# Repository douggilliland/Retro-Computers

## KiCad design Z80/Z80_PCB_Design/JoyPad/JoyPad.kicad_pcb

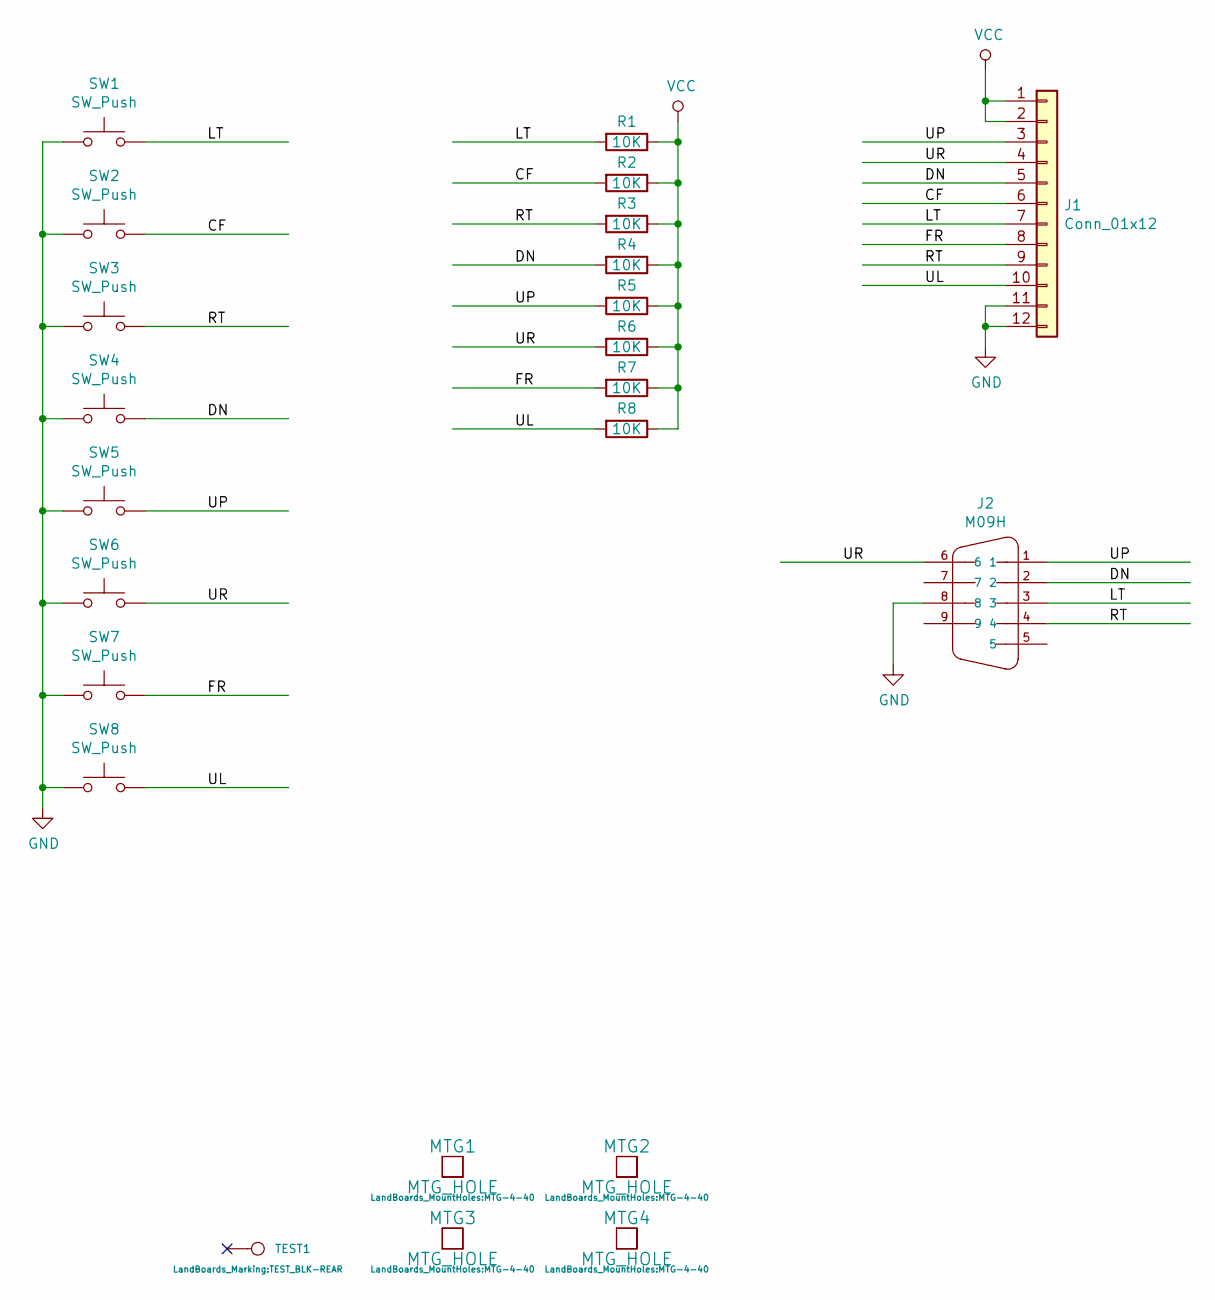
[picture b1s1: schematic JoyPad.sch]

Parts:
J1: Conn_01x12; PinHeader_1x12_P2.54mm_Vertical
J2: M09H; DSUB-9_Male_Horizontal_P2.77x2.84mm_EdgePinOffset4.94mm_Hou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
MTG1, MTG2, MTG3, MTG4: MTG_HOLE; MTG-4-40
R1, R2, R3, R4, R5, R6, R7, R8: 10K; R_0805_2012Metric_Pad1.15x1.40mm_HandSolder
SW1, SW2, SW3, SW4, SW5, SW6, SW7, SW8: SW_Push; SW_PUSH_6mm
TEST1: CONN_1; TEST_BLK-REAR

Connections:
/CF: J1.6, R2.2, SW2.2
/DN: J1.5, J2.2, R4.2, SW4.2
/FR: J1.8, R7.2, SW7.2
/LT: J1.7, J2.3, R1.2, SW1.2
/RT: J1.9, J2.4, R3.2, SW3.2
/UL: J1.10, R8.2, SW8.2
/UP: J1.3, J2.1, R5.2, SW5.2
/UR: J1.4, J2.6, R6.2, SW6.2
GND: J1.11, J1.12, J2.8, SW1.1, SW2.1, SW3.1, SW4.1, SW5.1, SW6.1, SW7.1, SW8.1
VCC: J1.1, J1.2, R1.1, R2.1, R3.1, R4.1, R5.1, R6.1, R7.1, R8.1

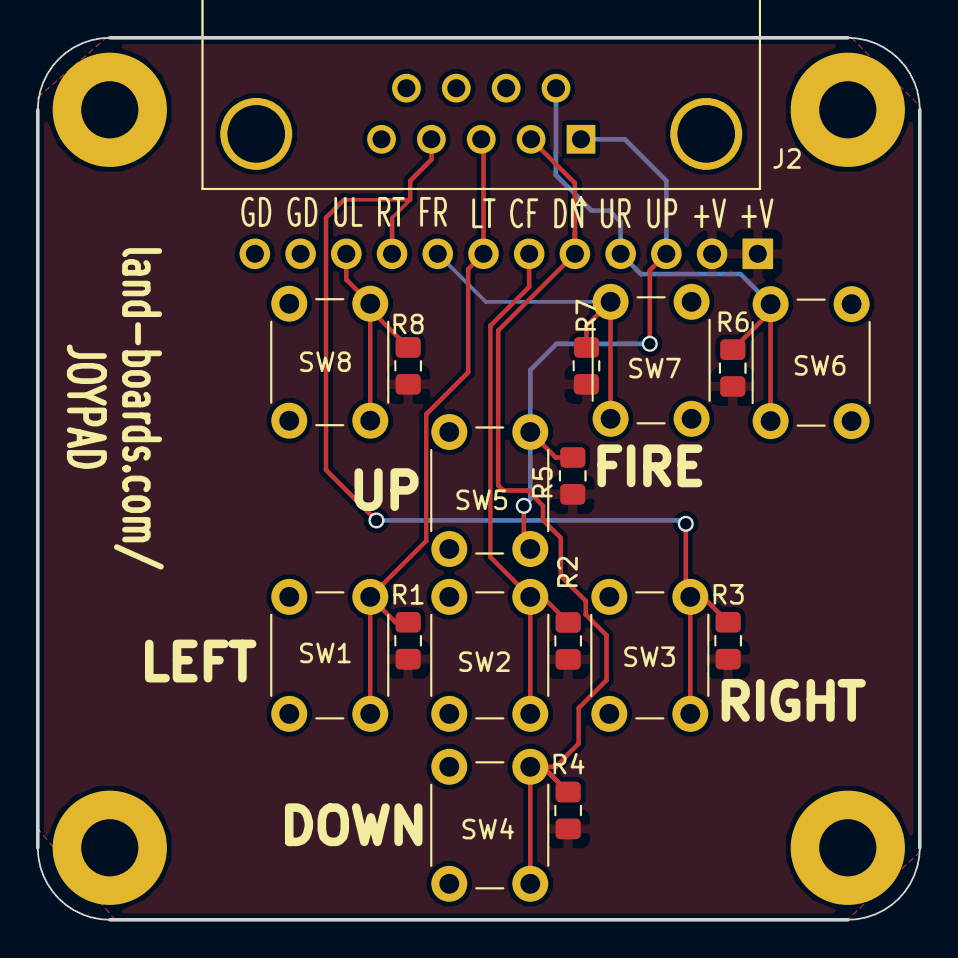
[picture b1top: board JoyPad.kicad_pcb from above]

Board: 2 copper layers, 49.0 x 49.0 mm, 23 parts (1 on the bottom side), 10 nets.

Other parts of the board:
TEST: CONN_1; TEST_BLK-REAR

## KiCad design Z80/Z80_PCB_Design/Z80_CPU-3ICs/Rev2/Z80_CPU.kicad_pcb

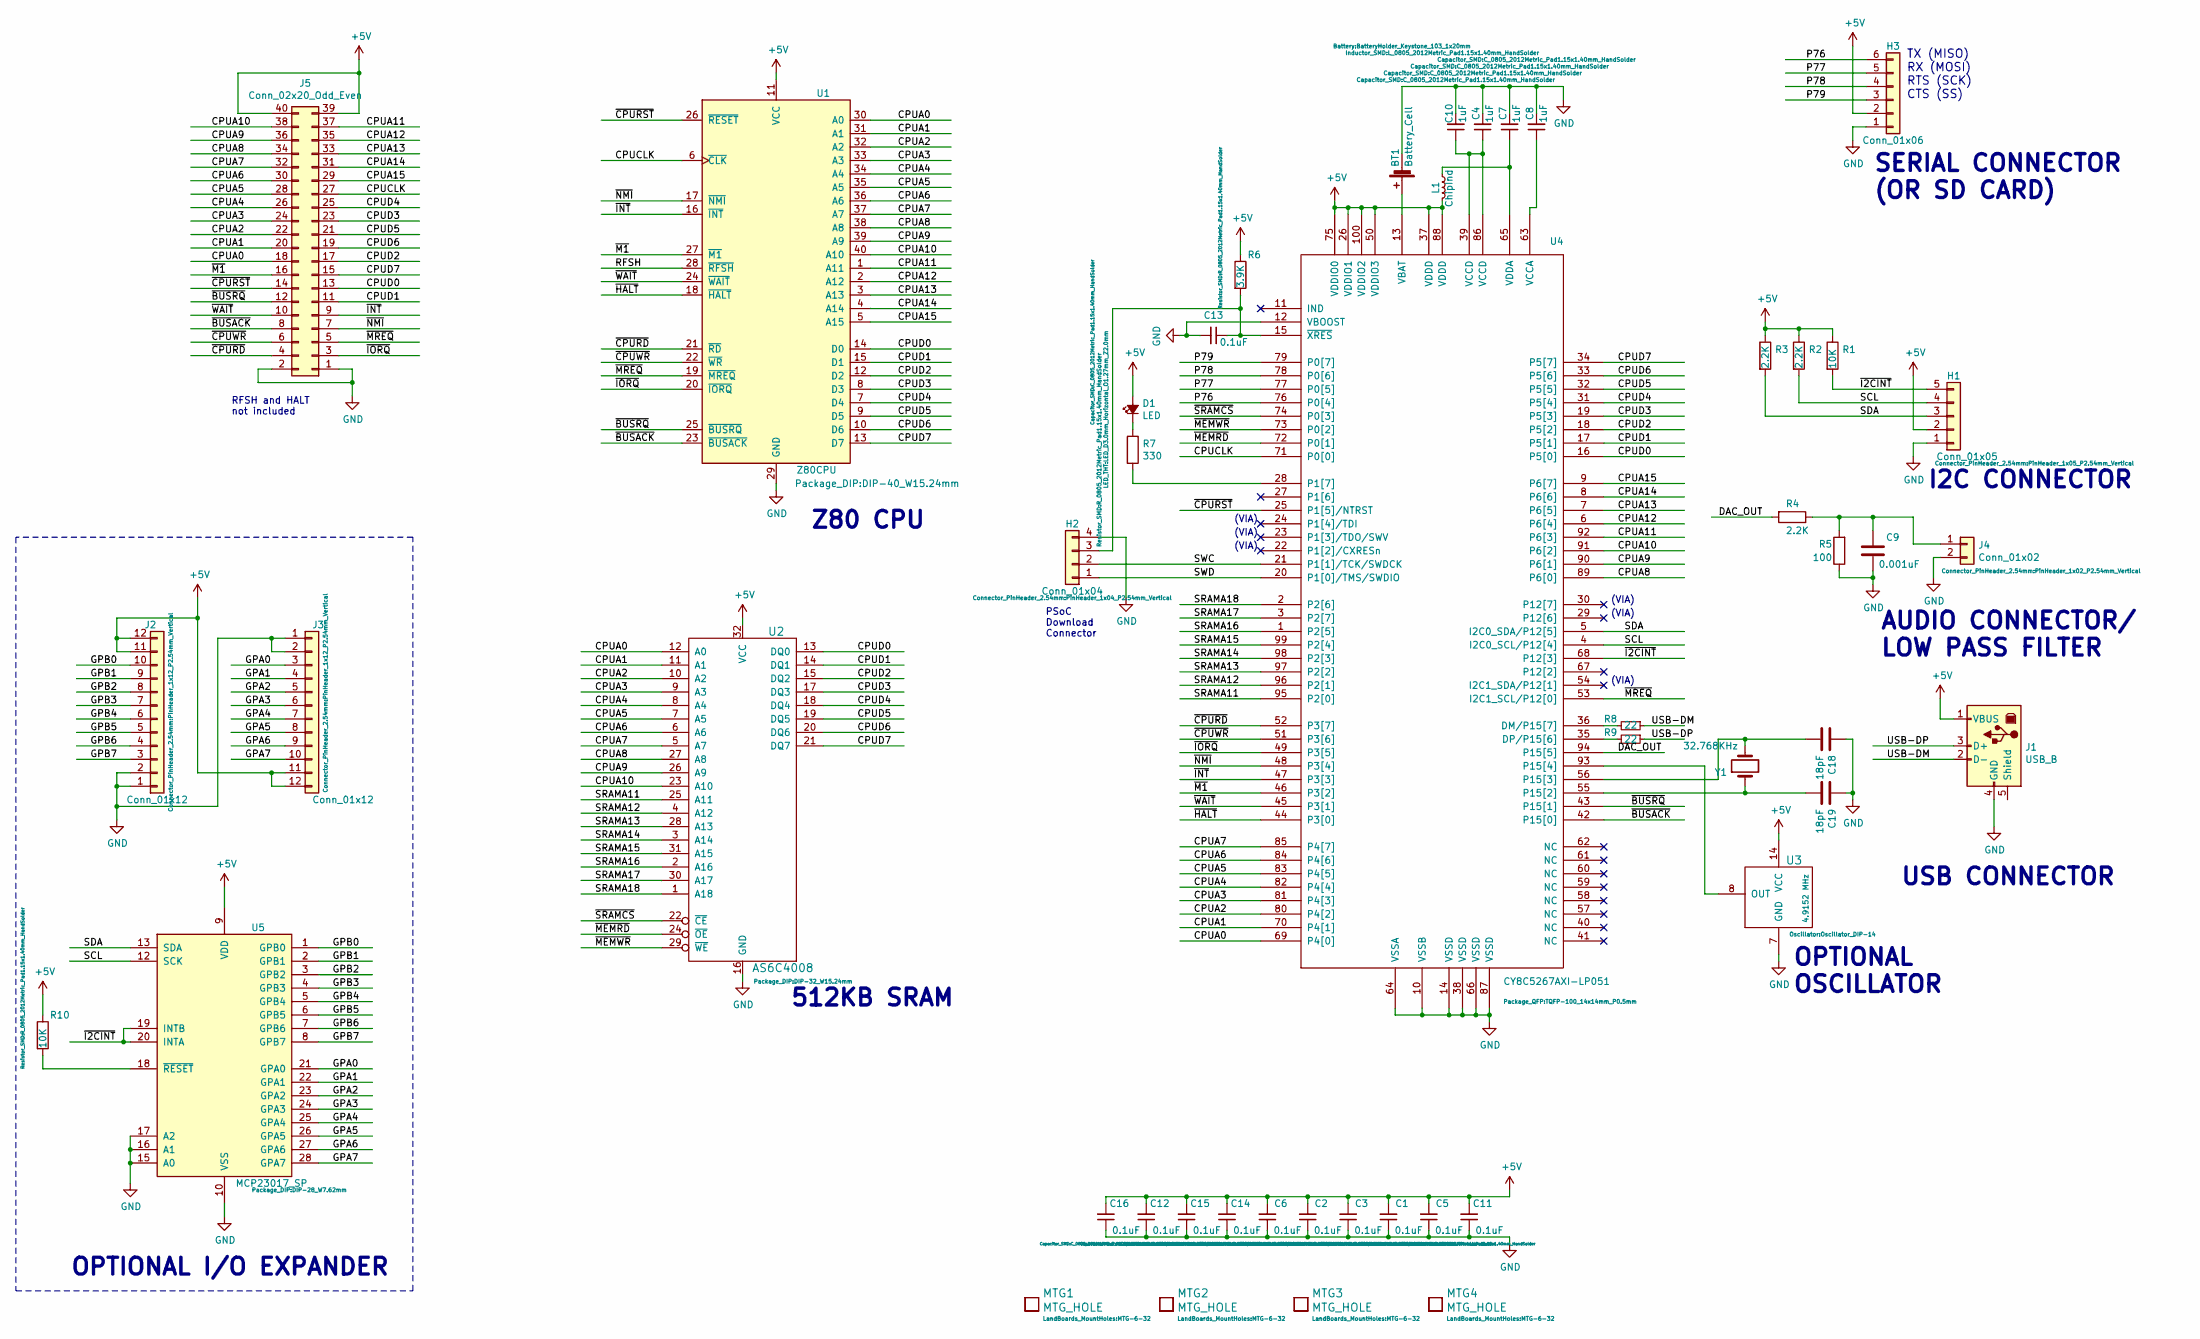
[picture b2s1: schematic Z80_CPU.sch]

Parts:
BT1: Battery_Cell; BatteryHolder_Keystone_103_1x20mm
C1, C2, C3, C5, C6, C11, C12, C13, C14, C15, C16: 0.1uF; C_0805_2012Metric_Pad1.15x1.40mm_HandSolder
C4, C7, C8, C10: 1uF; C_0805_2012Metric_Pad1.15x1.40mm_HandSolder
C9: 0.001uF; C_0805_2012Metric_Pad1.15x1.40mm_HandSolder
C18, C19: 18pF; C_0805_2012Metric_Pad1.15x1.40mm_HandSolder
D1: LED; LED_D3.0mm_Horizontal_O1.27mm_Z2.0mm
H1: Conn_01x05; PinHeader_1x05_P2.54mm_Vertical
H2: Conn_01x04; PinHeader_1x04_P2.54mm_Vertical
H3: Conn_01x06; PinHeader_1x06_P2.54mm_Vertical
J1: USB_B; USB_B_OST_USB-B1HSxx_Horizontal
J2, J3: Conn_01x12; PinHeader_1x12_P2.54mm_Vertical
J4: Conn_01x02; PinHeader_1x02_P2.54mm_Vertical
J5: Conn_02x20_Odd_Even; PinHeader_2x20_P2.54mm_Horizontal
L1: ChipInd; L_0805_2012Metric_Pad1.15x1.40mm_HandSolder
MTG1, MTG2, MTG3, MTG4: MTG_HOLE; MTG-6-32
R1, R10: 10K; R_0805_2012Metric_Pad1.15x1.40mm_HandSolder
R2, R3, R4: 2.2K; R_0805_2012Metric_Pad1.15x1.40mm_HandSolder
R5: 100; R_0805_2012Metric_Pad1.15x1.40mm_HandSolder
R6: 3.9K; R_0805_2012Metric_Pad1.15x1.40mm_HandSolder
R7: 330; R_0805_2012Metric_Pad1.15x1.40mm_HandSolder
R8, R9: 22; R_0805_2012Metric_Pad1.15x1.40mm_HandSolder
U1: Z80CPU; DIP-40_W15.24mm
U2: AS6C4008; DIP-32_W15.24mm
U3: 4.9152 MHz; Oscillator_DIP-14
U4: CY8C5267AXI-LP051; TQFP-100_14x14mm_P0.5mm
U5: MCP23017_SP; DIP-28_W7.62mm
Y1: 32.768KHz; Crystal_C26-LF_D2.1mm_L6.5mm_Horizontal

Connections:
+5V: C1.2, C2.2, C3.2, C5.2, C6.2, C11.2, C12.2, C14.2, C15.2, C16.2, D1.2 (A), H1.2, H3.2, J1.1 (VBUS), J2.11, J2.12, J3.11, J3.12, J5.39, J5.40, L1.2, R1.1, R2.1, R3.1, R6.1, R10.1, U1.11 (VCC), U2.32 (VCC), U3.14 (VCC), U4.26 (VDDIO1), U4.37 (VDDD), U4.50 (VDDIO3), U4.75 (VDDIO0), U4.88 (VDDD), U4.100 (VDDIO2), U5.9 (VDD)
/CPUA0: J5.18, U1.30 (A0), U2.12 (A0), U4.69 (P4[0])
/CPUA1: J5.20, U1.31 (A1), U2.11 (A1), U4.70 (P4[1])
/CPUA2: J5.22, U1.32 (A2), U2.10 (A2), U4.80 (P4[2])
/CPUA3: J5.24, U1.33 (A3), U2.9 (A3), U4.81 (P4[3])
/CPUA4: J5.26, U1.34 (A4), U2.8 (A4), U4.82 (P4[4])
/CPUA5: J5.28, U1.35 (A5), U2.7 (A5), U4.83 (P4[5])
/CPUA6: J5.30, U1.36 (A6), U2.6 (A6), U4.84 (P4[6])
/CPUA7: J5.32, U1.37 (A7), U2.5 (A7), U4.85 (P4[7])
/CPUA8: J5.34, U1.38 (A8), U2.27 (A8), U4.89 (P6[0])
/CPUA9: J5.36, U1.39 (A9), U2.26 (A9), U4.90 (P6[1])
/CPUA10: J5.38, U1.40 (A10), U2.23 (A10), U4.91 (P6[2])
/CPUA11: J5.37, U1.1 (A11), U4.92 (P6[3])
/CPUA12: J5.35, U1.2 (A12), U4.6 (P6[4])
/CPUA13: J5.33, U1.3 (A13), U4.7 (P6[5])
/CPUA14: J5.31, U1.4 (A14), U4.8 (P6[6])
/CPUA15: J5.29, U1.5 (A15), U4.9 (P6[7])
/CPUCLK: J5.27, U1.6 (~CLK), U4.71 (P0[0])
/CPUD0: J5.13, U1.14 (D0), U2.13 (DQ0), U4.16 (P5[0])
/CPUD1: J5.11, U1.15 (D1), U2.14 (DQ1), U4.17 (P5[1])
/CPUD2: J5.17, U1.12 (D2), U2.15 (DQ2), U4.18 (P5[2])
/CPUD3: J5.23, U1.8 (D3), U2.17 (DQ3), U4.19 (P5[3])
/CPUD4: J5.25, U1.7 (D4), U2.18 (DQ4), U4.31 (P5[4])
/CPUD5: J5.21, U1.9 (D5), U2.19 (DQ5), U4.32 (P5[5])
/CPUD6: J5.19, U1.10 (D6), U2.20 (DQ6), U4.33 (P5[6])
/CPUD7: J5.15, U1.13 (D7), U2.21 (DQ7), U4.34 (P5[7])
/DAC_OUT: R4.2, U4.94 (P15[5])
/GPA0: J3.3, U5.21 (GPA0)
/GPA1: J3.4, U5.22 (GPA1)
/GPA2: J3.5, U5.23 (GPA2)
/GPA3: J3.6, U5.24 (GPA3)
/GPA4: J3.7, U5.25 (GPA4)
/GPA5: J3.8, U5.26 (GPA5)
/GPA6: J3.9, U5.27 (GPA6)
/GPA7: J3.10, U5.28 (GPA7)
/GPB0: J2.10, U5.1 (GPB0)
/GPB1: J2.9, U5.2 (GPB1)
/GPB2: J2.8, U5.3 (GPB2)
/GPB3: J2.7, U5.4 (GPB3)
/GPB4: J2.6, U5.5 (GPB4)
/GPB5: J2.5, U5.6 (GPB5)
/GPB6: J2.4, U5.7 (GPB6)
/GPB7: J2.3, U5.8 (GPB7)
/P76: H3.6, U4.76 (P0[4])
/P77: H3.5, U4.77 (P0[5])
/P78: H3.4, U4.78 (P0[6])
/P79: H3.3, U4.79 (P0[7])
/SCL: H1.4, R2.2, U4.4 (I2C0_SCL/P12[4]), U5.12 (SCK)
/SDA: H1.3, R3.2, U4.5 (I2C0_SDA/P12[5]), U5.13 (SDA)
/SRAMA11: U2.25 (A11), U4.95 (P2[0])
/SRAMA12: U2.4 (A12), U4.96 (P2[1])
/SRAMA13: U2.28 (A13), U4.97 (P2[2])
/SRAMA14: U2.3 (A14), U4.98 (P2[3])
/SRAMA15: U2.31 (A15), U4.99 (P2[4])
/SRAMA16: U2.2 (A16), U4.1 (P2[5])
/SRAMA17: U2.30 (A17), U4.3 (P2[7])
/SRAMA18: U2.1 (A18), U4.2 (P2[6])
/SWC: H2.2, U4.21 (P1[1]/TCK/SWDCK)
/SWD: H2.1, U4.20 (P1[0]/TMS/SWDIO)
/USB-DM: J1.2 (D-), R8.1
/USB-DP: J1.3 (D+), R9.1
/~BUSACK: J5.8, U1.23 (~BUSACK), U4.42 (P15[0])
/~BUSRQ: J5.12, U1.25 (~BUSRQ), U4.43 (P15[1])
/~CPURD: J5.4, U1.21 (~RD), U4.52 (P3[7])
/~CPURST: J5.14, R10.2, U1.26 (~RESET), U4.25 (P1[5]/NTRST), U5.18 (~RESET~)
/~CPUWR: J5.6, U1.22 (~WR), U4.51 (P3[6])
/~HALT: U1.18 (~HALT), U4.44 (P3[0])
/~I2CINT: H1.5, R1.2, U4.68 (P12[3]), U5.19 (INTB), U5.20 (INTA)
/~INT: J5.9, U1.16 (~INT), U4.47 (P3[3])
/~IORQ: J5.3, U1.20 (~IORQ), U4.49 (P3[5])
/~M1: J5.16, U1.27 (~M1~), U4.46 (P3[2])
/~MEMRD: U2.24 (~OE), U4.72 (P0[1])
/~MEMWR: U2.29 (~WE), U4.73 (P0[2])
/~MREQ: J5.5, U1.19 (~MREQ), U4.53 (I2C1_SCL/P12[0])
/~NMI: J5.7, U1.17 (~NMI), U4.48 (P3[4])
/~SRAMCS: U2.22 (~CE), U4.74 (P0[3])
/~WAIT: J5.10, U1.24 (~WAIT~), U4.45 (P3[1])
GND: BT1.2 (-), C1.1, C2.1, C3.1, C4.2, C5.1, C6.1, C7.2, C8.2, C9.1, C10.2, C11.1, C12.1, C13.2, C14.1, C15.1, C16.1, C18.1, C19.1, H1.1, H2.4, H3.1, J1.4 (GND), J2.1, J2.2, J3.1, J3.2, J4.2, J5.1, J5.2, R5.1, U1.29 (GND), U2.16 (GND), U3.7 (GND), U4.10 (VSSB), U4.12 (VBOOST), U4.14 (VSSD), U4.38 (VSSD), U4.64 (VSSA), U4.66 (VSSD), U4.87 (VSSD), U5.10 (VSS), U5.15 (A0), U5.16 (A1), U5.17 (A2)
unnamed: BT1.1 (+), U4.13 (VBAT)
unnamed: C7.1, L1.1, U4.65 (VDDA)
unnamed: C8.1, U4.63 (VCCA)
unnamed: C9.2, J4.1, R4.1, R5.2
unnamed: C4.1, C10.1, U4.39 (VCCD), U4.86 (VCCD)
unnamed: C13.1, H2.3, R6.2, U4.15 (~XRES)
unnamed: C18.2, U4.56 (P15[3]), Y1.2
unnamed: C19.2, U4.55 (P15[2]), Y1.1
unnamed: D1.1 (K), R7.1
unnamed: R7.2, U4.28 (P1[7])
unnamed: R8.2, U4.36 (DM/P15[7])
unnamed: R9.2, U4.35 (DP/P15[6])
unnamed: U3.8 (OUT), U4.93 (P15[4])

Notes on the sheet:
PSoC Download Connector
(VIA)
OPTIONAL I/O EXPANDER
SERIAL CONNECTOR (OR SD CARD)
I2C CONNECTOR
512KB SRAM
Z80 CPU
AUDIO CONNECTOR/ LOW PASS FILTER
USB CONNECTOR
OPTIONAL OSCILLATOR
TX (MISO) RX (MOSI) RTS (SCK) CTS (SS)
RFSH and HALT not included

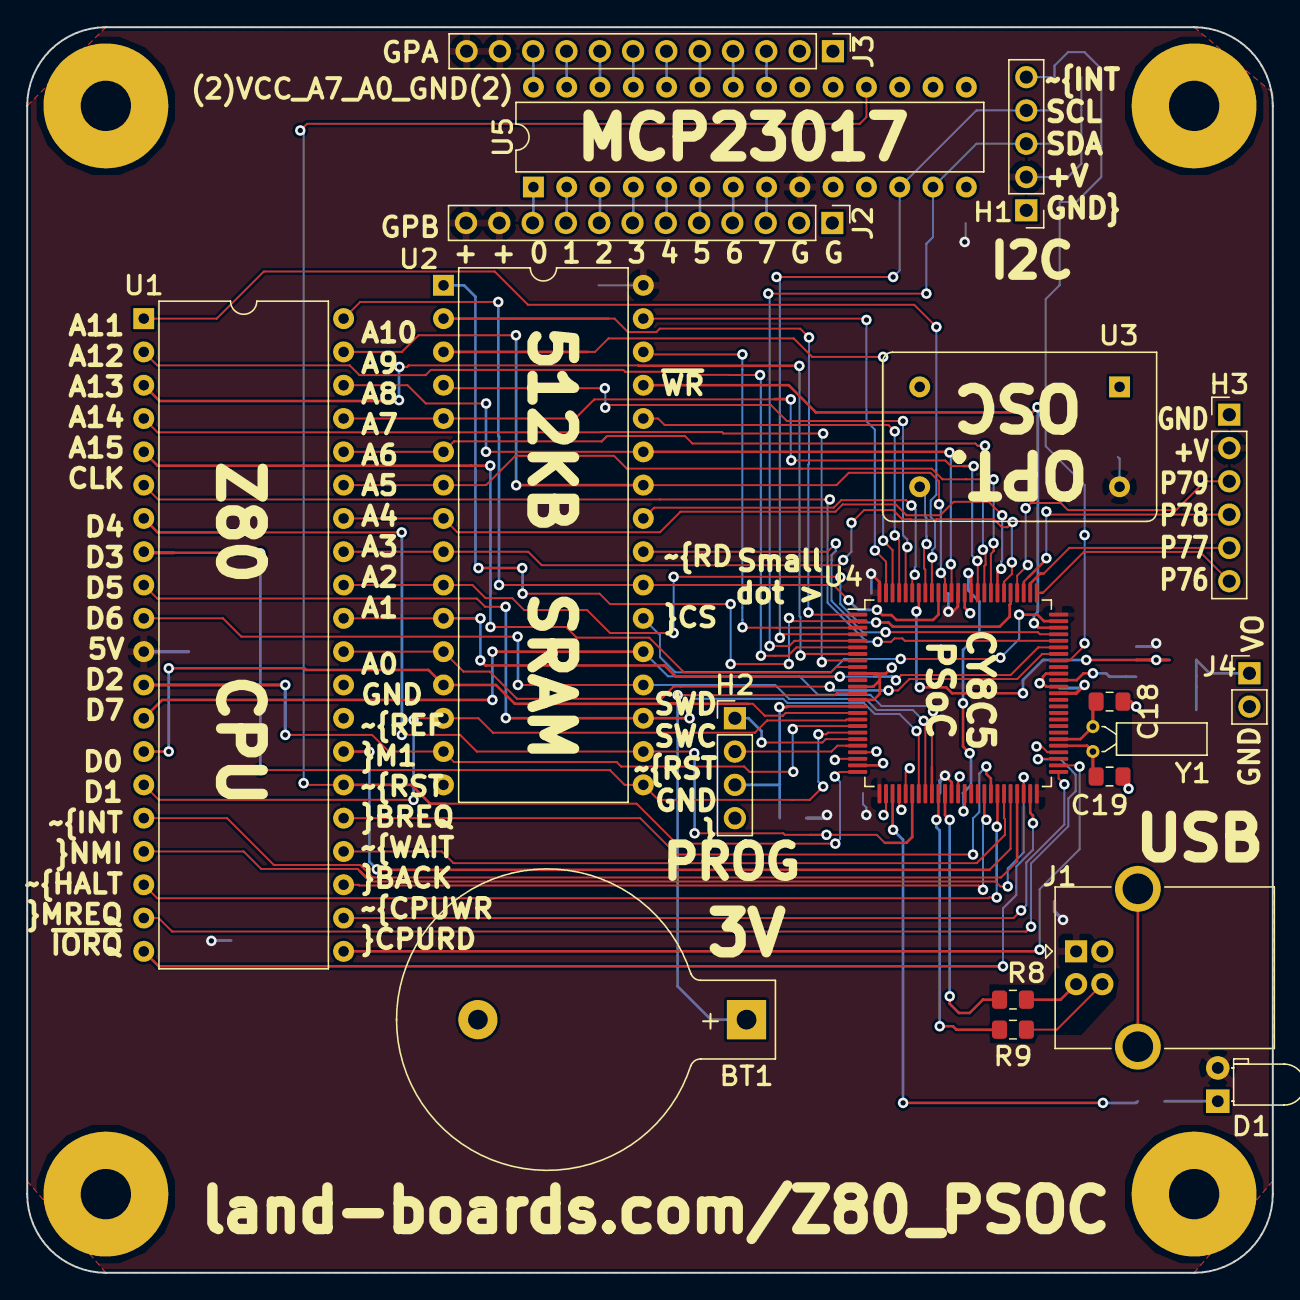
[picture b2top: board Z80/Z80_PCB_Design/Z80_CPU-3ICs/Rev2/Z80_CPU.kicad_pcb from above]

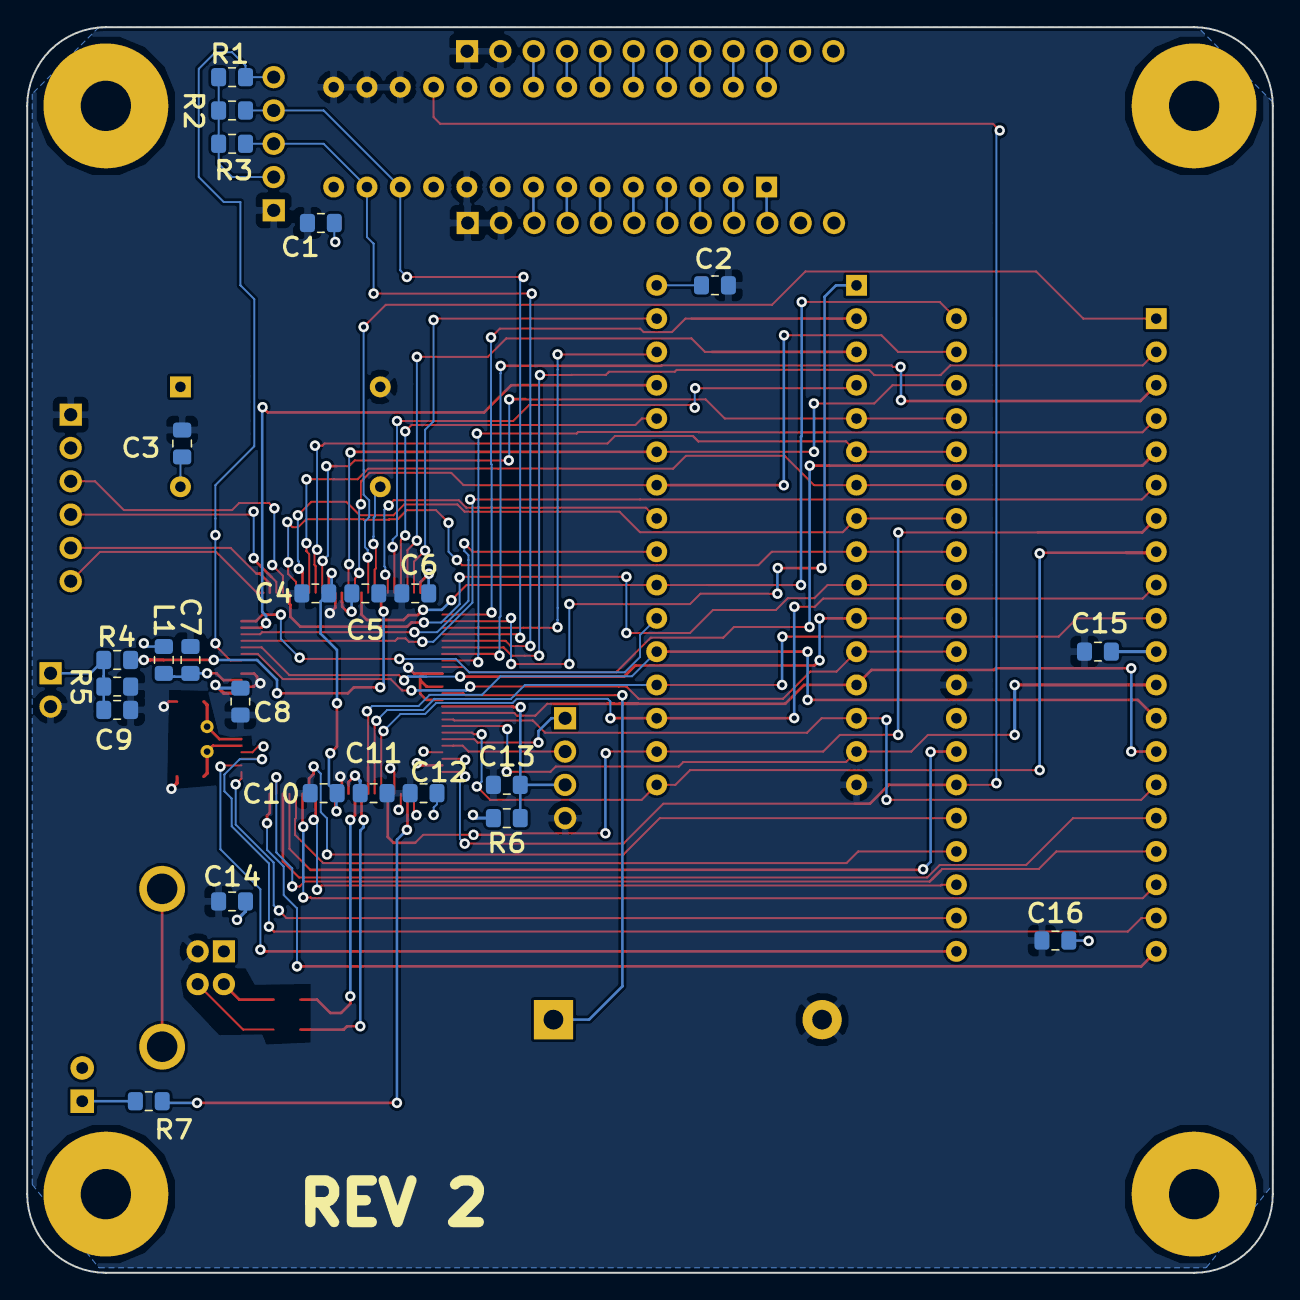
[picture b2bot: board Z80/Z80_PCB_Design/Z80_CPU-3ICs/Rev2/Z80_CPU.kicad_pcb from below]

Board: 2 copper layers, 95.0 x 95.0 mm, 47 parts (24 on the bottom side), 91 nets.

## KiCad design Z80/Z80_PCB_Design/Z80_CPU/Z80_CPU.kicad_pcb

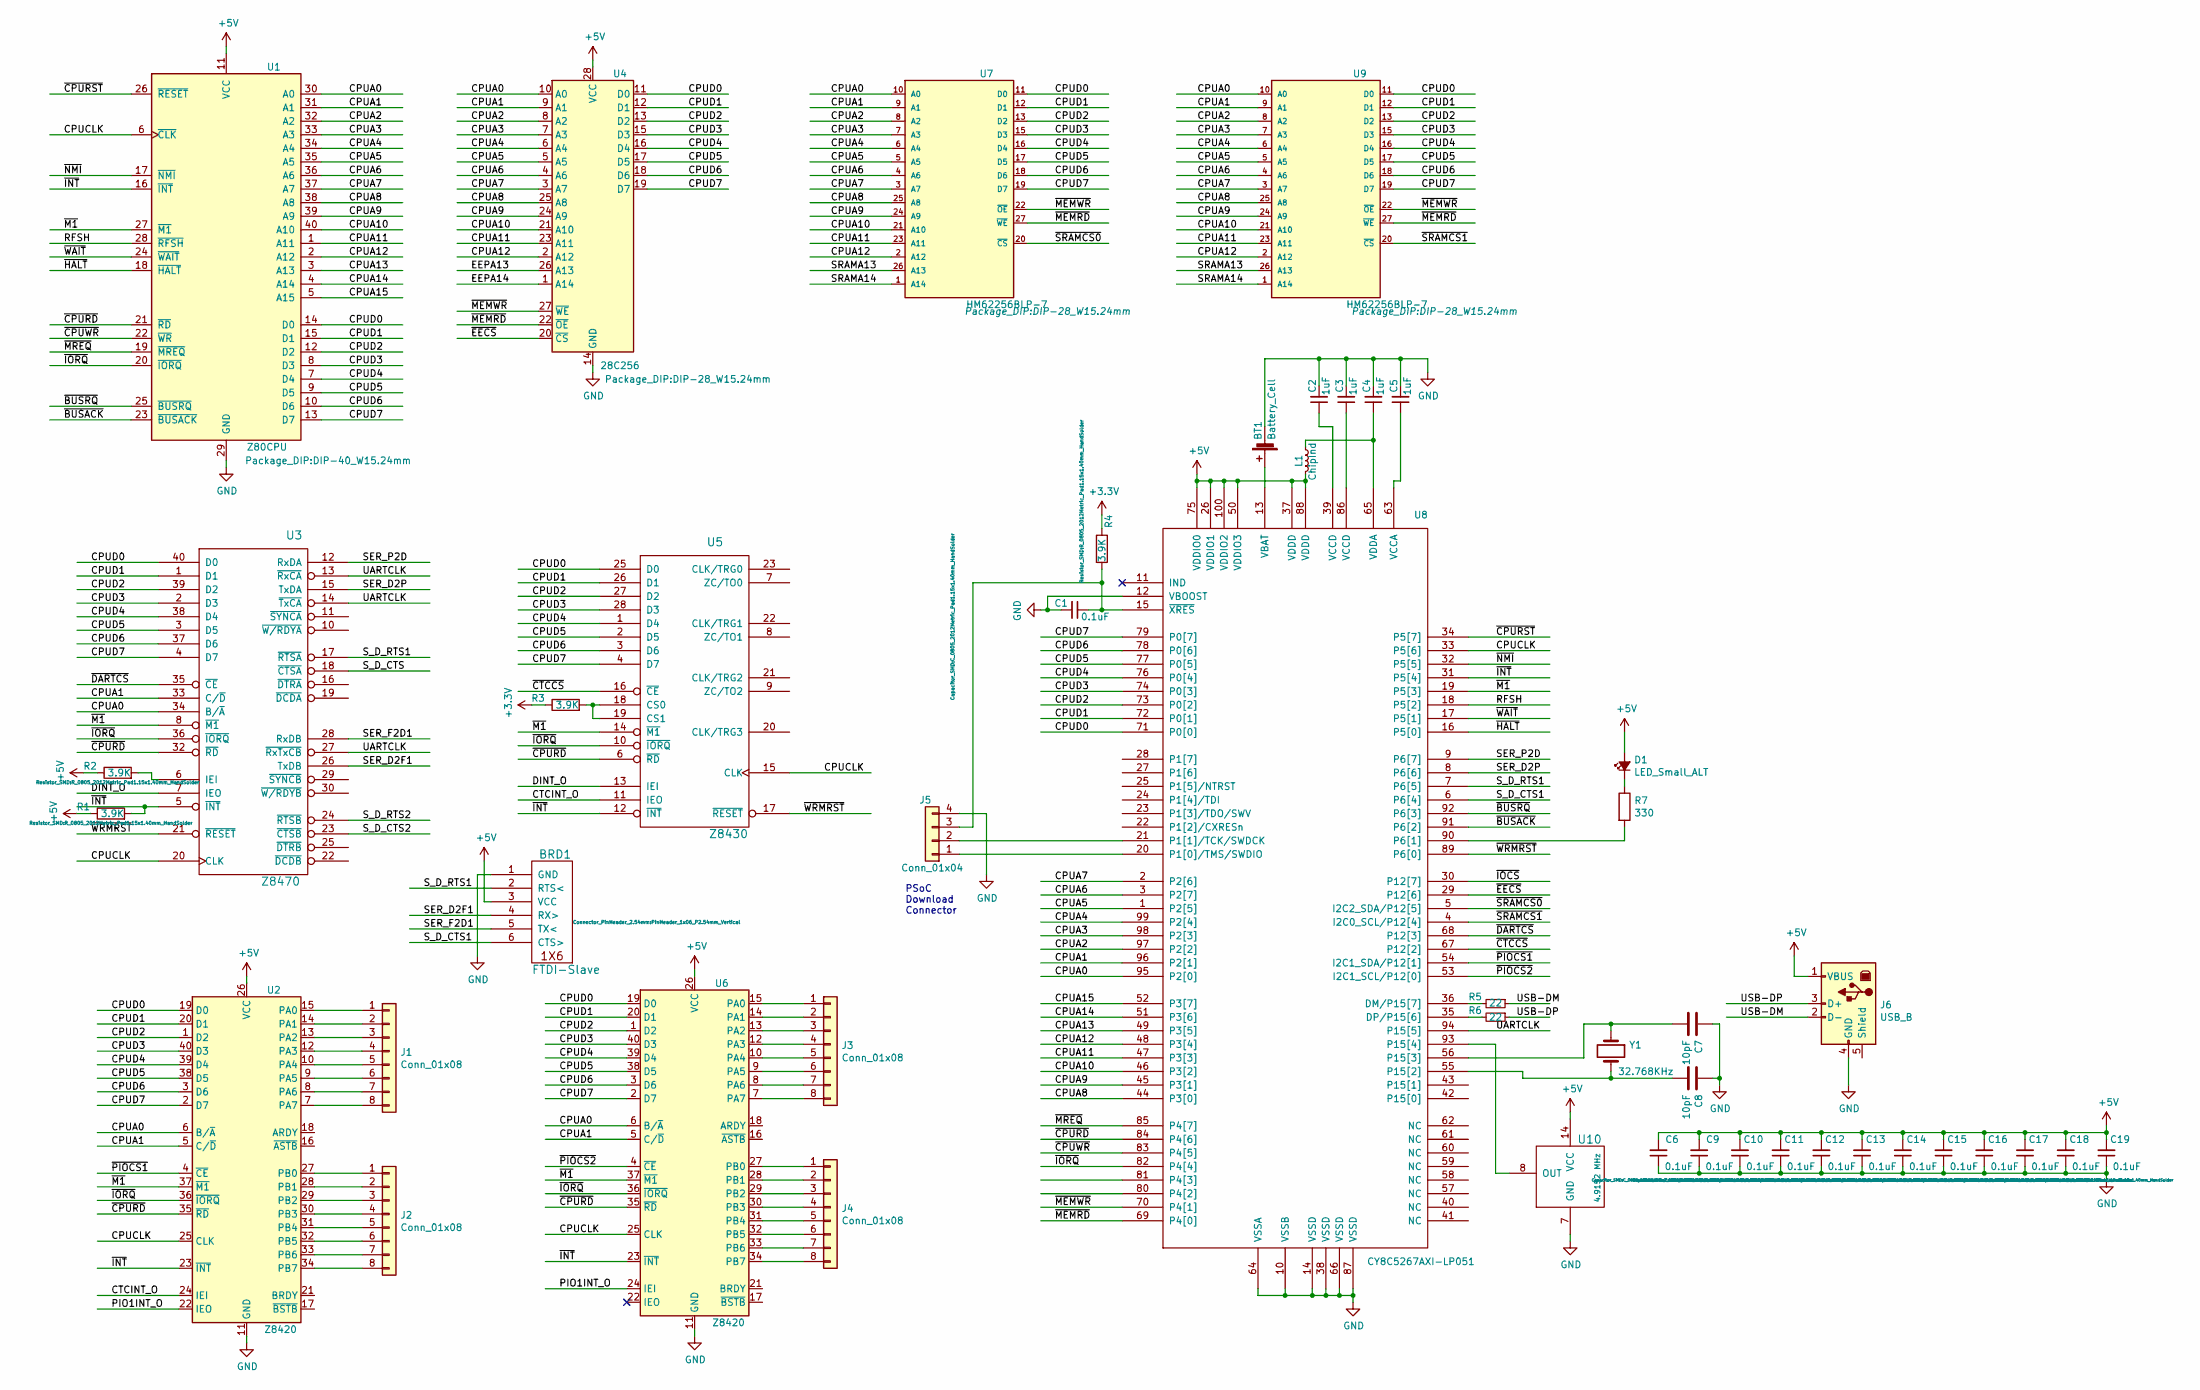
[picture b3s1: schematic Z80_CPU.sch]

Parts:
BRD1: FTDI-Slave; PinHeader_1x06_P2.54mm_Vertical
BT1: Battery_Cell; BatteryHolder_Keystone_1060_1x2032
C1, C6, C9, C10, C11, C12, C13, C14, C15, C16, C17, C18, C19: 0.1uF; C_0805_2012Metric_Pad1.15x1.40mm_HandSolder
C2, C3, C4, C5: 1uF; C_0805_2012Metric_Pad1.15x1.40mm_HandSolder
C7, C8: 10pF; C_0805_2012Metric_Pad1.15x1.40mm_HandSolder
D1: LED_Small_ALT; LED_D3.0mm_Horizontal_O1.27mm_Z2.0mm
J1, J2, J3, J4: Conn_01x08; PinHeader_1x08_P2.54mm_Vertical
J5: Conn_01x04; PinHeader_1x04_P2.54mm_Vertical
J6: USB_B; USB_B_OST_USB-B1HSxx_Horizontal
L1: ChipInd; L_0805_2012Metric_Pad1.15x1.40mm_HandSolder
R1, R2, R3, R4: 3.9K; R_0805_2012Metric_Pad1.15x1.40mm_HandSolder
R5, R6: 22; R_0805_2012Metric_Pad1.15x1.40mm_HandSolder
R7: 330; R_0805_2012Metric_Pad1.15x1.40mm_HandSolder
U1: Z80CPU; DIP-40_W15.24mm
U2, U6: Z8420; DIP-40_W15.24mm
U3: Z8470; DIP-40_W15.24mm
U4: 28C256; DIP-28_W15.24mm
U5: Z8430; DIP-28_W15.24mm
U7, U9: HM62256BLP-7; DIP-28_W15.24mm
U8: CY8C5267AXI-LP051; TQFP-100_14x14mm_P0.5mm
U10: 4.9152 MHz; Oscillator_DIP-14
Y1: 32.768KHz; Crystal_HC18-U_Horizontal

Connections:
+3V3: R3.1, R4.1
+5V: BRD1.3 (VCC), C6.2, C9.2, C10.2, C11.2, C12.2, C13.2, C14.2, C15.2, C16.2, C17.2, C18.2, C19.2, D1.2 (A), J6.1 (VBUS), L1.2, R1.1, R2.1, U1.11 (VCC), U2.26 (VCC), U4.28 (VCC), U6.26 (VCC), U8.26 (VDDIO1), U8.37 (VDDD), U8.50 (VDDIO3), U8.75 (VDDIO0), U8.88 (VDDD), U8.100 (VDDIO2), U10.14 (VCC)
/CPUA0: U1.30 (A0), U2.6 (B/~A~), U3.34 (B/~A), U4.10 (A0), U6.6 (B/~A~), U7.10 (A0), U8.95 (P2[0]), U9.10 (A0)
/CPUA1: U1.31 (A1), U2.5 (C/~D~), U3.33 (C/~D), U4.9 (A1), U6.5 (C/~D~), U7.9 (A1), U8.96 (P2[1]), U9.9 (A1)
/CPUA2: U1.32 (A2), U4.8 (A2), U7.8 (A2), U8.97 (P2[2]), U9.8 (A2)
/CPUA3: U1.33 (A3), U4.7 (A3), U7.7 (A3), U8.98 (P2[3]), U9.7 (A3)
/CPUA4: U1.34 (A4), U4.6 (A4), U7.6 (A4), U8.99 (P2[4]), U9.6 (A4)
/CPUA5: U1.35 (A5), U4.5 (A5), U7.5 (A5), U8.1 (P2[5]), U9.5 (A5)
/CPUA6: U1.36 (A6), U4.4 (A6), U7.4 (A6), U8.3 (P2[7]), U9.4 (A6)
/CPUA7: U1.37 (A7), U4.3 (A7), U7.3 (A7), U8.2 (P2[6]), U9.3 (A7)
/CPUA8: U1.38 (A8), U4.25 (A8), U7.25 (A8), U8.44 (P3[0]), U9.25 (A8)
/CPUA9: U1.39 (A9), U4.24 (A9), U7.24 (A9), U8.45 (P3[1]), U9.24 (A9)
/CPUA10: U1.40 (A10), U4.21 (A10), U7.21 (A10), U8.46 (P3[2]), U9.21 (A10)
/CPUA11: U1.1 (A11), U4.23 (A11), U7.23 (A11), U8.47 (P3[3]), U9.23 (A11)
/CPUA12: U1.2 (A12), U4.2 (A12), U7.2 (A12), U8.48 (P3[4]), U9.2 (A12)
/CPUA13: U1.3 (A13), U8.49 (P3[5])
/CPUA14: U1.4 (A14), U8.51 (P3[6])
/CPUA15: U1.5 (A15), U8.52 (P3[7])
/CPUCLK: U1.6 (~CLK), U2.25 (CLK), U3.20 (CLK), U5.15 (CLK), U6.25 (CLK), U8.33 (P5[6])
/CPUD0: U1.14 (D0), U2.19 (D0), U3.40 (D0), U4.11 (D0), U5.25 (D0), U6.19 (D0), U7.11 (D0), U8.71 (P0[0]), U9.11 (D0)
/CPUD1: U1.15 (D1), U2.20 (D1), U3.1 (D1), U4.12 (D1), U5.26 (D1), U6.20 (D1), U7.12 (D1), U8.72 (P0[1]), U9.12 (D1)
/CPUD2: U1.12 (D2), U2.1 (D2), U3.39 (D2), U4.13 (D2), U5.27 (D2), U6.1 (D2), U7.13 (D2), U8.73 (P0[2]), U9.13 (D2)
/CPUD3: U1.8 (D3), U2.40 (D3), U3.2 (D3), U4.15 (D3), U5.28 (D3), U6.40 (D3), U7.15 (D3), U8.74 (P0[3]), U9.15 (D3)
/CPUD4: U1.7 (D4), U2.39 (D4), U3.38 (D4), U4.16 (D4), U5.1 (D4), U6.39 (D4), U7.16 (D4), U8.76 (P0[4]), U9.16 (D4)
/CPUD5: U1.9 (D5), U2.38 (D5), U3.3 (D5), U4.17 (D5), U5.2 (D5), U6.38 (D5), U7.17 (D5), U8.77 (P0[5]), U9.17 (D5)
/CPUD6: U1.10 (D6), U2.3 (D6), U3.37 (D6), U4.18 (D6), U5.3 (D6), U6.3 (D6), U7.18 (D6), U8.78 (P0[6]), U9.18 (D6)
/CPUD7: U1.13 (D7), U2.2 (D7), U3.4 (D7), U4.19 (D7), U5.4 (D7), U6.2 (D7), U7.19 (D7), U8.79 (P0[7]), U9.19 (D7)
/CTCINT_O: U2.24 (IEI), U5.11 (IEO)
/DINT_O: U3.7 (IEO), U5.13 (IEI)
/PIO1INT_O: U2.22 (IEO), U6.24 (IEI)
/RFSH: U1.28 (~RFSH), U8.18 (P5[2])
/SER_D2F1: BRD1.4 (RX>), U3.26 (TxDB)
/SER_D2P: U3.15 (TxDA), U8.8 (P6[6])
/SER_F2D1: BRD1.5 (TX<), U3.28 (RxDB)
/SER_P2D: U3.12 (RxDA), U8.9 (P6[7])
/SRAMA13: U7.26 (A13), U9.26 (A13)
/SRAMA14: U7.1 (A14), U9.1 (A14)
/S_D_CTS1: BRD1.6 (CTS>), U8.6 (P6[4])
/S_D_RTS1: BRD1.2 (RTS<), U3.17 (~RTSA), U8.7 (P6[5])
/UARTCLK: U3.13 (~RxCA), U3.14 (~TxCA), U3.27 (~RxTxCB), U8.94 (P15[5])
/USB-DM: J6.2 (D-), R5.1
/USB-DP: J6.3 (D+), R6.1
/~BUSACK: U1.23 (~BUSACK), U8.91 (P6[2])
/~BUSRQ: U1.25 (~BUSRQ), U8.92 (P6[3])
/~CPURD: U1.21 (~RD), U2.35 (~RD~), U3.32 (~RD), U5.6 (~RD), U6.35 (~RD~), U8.84 (P4[6])
/~CPURST: U1.26 (~RESET), U8.34 (P5[7])
/~CPUWR: U1.22 (~WR), U8.83 (P4[5])
/~CTCCS: U5.16 (~CE), U8.67 (P12[2])
/~DARTCS: U3.35 (~CE), U8.68 (P12[3])
/~EECS: U4.20 (~CS), U8.29 (P12[6])
/~HALT: U1.18 (~HALT), U8.16 (P5[0])
/~INT: R1.2, U1.16 (~INT), U2.23 (~INT~), U3.5 (~INT), U5.12 (~INT), U6.23 (~INT~), U8.31 (P5[4])
/~IORQ: U1.20 (~IORQ), U2.36 (~IORQ~), U3.36 (~IORQ), U5.10 (~IORQ), U6.36 (~IORQ~), U8.82 (P4[4])
/~M1: U1.27 (~M1~), U2.37 (~M1~), U3.8 (~M1), U5.14 (~M1), U6.37 (~M1~), U8.19 (P5[3])
/~MEMRD: U4.22 (~OE), U7.27 (~WE), U8.69 (P4[0]), U9.27 (~WE)
/~MEMWR: U4.27 (~WE), U7.22 (~OE), U8.70 (P4[1]), U9.22 (~OE)
/~MREQ: U1.19 (~MREQ), U8.85 (P4[7])
/~NMI: U1.17 (~NMI), U8.32 (P5[5])
/~PIOCS1: U2.4 (~CE~), U8.54 (I2C1_SDA/P12[1])
/~PIOCS2: U6.4 (~CE~), U8.53 (I2C1_SCL/P12[0])
/~SRAMCS0: U7.20 (~CS), U8.5 (I2C2_SDA/P12[5])
/~SRAMCS1: U8.4 (I2C0_SCL/P12[4]), U9.20 (~CS)
/~WAIT: U1.24 (~WAIT~), U8.17 (P5[1])
/~WRMRST: U3.21 (~RESET), U5.17 (~RESET), U8.89 (P6[0])
GND: BRD1.1 (GND), BT1.2 (-), C1.2, C2.2, C3.2, C4.2, C5.2, C6.1, C7.1, C8.1, C9.1, C10.1, C11.1, C12.1, C13.1, C14.1, C15.1, C16.1, C17.1, C18.1, C19.1, J5.4, J6.4 (GND), U1.29 (GND), U2.11 (GND), U3.31 (GND), U4.14 (GND), U5.5 (GND), U6.11 (GND), U7.14 (GND), U8.10 (VSSB), U8.12 (VBOOST), U8.14 (VSSD), U8.38 (VSSD), U8.64 (VSSA), U8.66 (VSSD), U8.87 (VSSD), U9.14 (GND), U10.7 (GND)
unnamed: BT1.1 (+), U8.13 (VBAT)
unnamed: C1.1, J5.3, R4.2, U8.15 (~XRES)
unnamed: C2.1, U8.39 (VCCD)
unnamed: C3.1, U8.86 (VCCD)
unnamed: C4.1, L1.1, U8.65 (VDDA)
unnamed: C5.1, U8.63 (VCCA)
unnamed: C7.2, U8.56 (P15[3]), Y1.1
unnamed: C8.2, U8.55 (P15[2]), Y1.2
unnamed: D1.1 (K), R7.1
unnamed: J1.1, U2.15 (PA0)
unnamed: J1.2, U2.14 (PA1)
unnamed: J1.3, U2.13 (PA2)
unnamed: J1.4, U2.12 (PA3)
unnamed: J1.5, U2.10 (PA4)
unnamed: J1.6, U2.9 (PA5)
unnamed: J1.7, U2.8 (PA6)
unnamed: J1.8, U2.7 (PA7)
unnamed: J2.1, U2.27 (PB0)
unnamed: J2.2, U2.28 (PB1)
unnamed: J2.3, U2.29 (PB2)
unnamed: J2.4, U2.30 (PB3)
unnamed: J2.5, U2.31 (PB4)
unnamed: J2.6, U2.32 (PB5)
unnamed: J2.7, U2.33 (PB6)
unnamed: J2.8, U2.34 (PB7)
unnamed: J3.1, U6.15 (PA0)
unnamed: J3.2, U6.14 (PA1)
unnamed: J3.3, U6.13 (PA2)
unnamed: J3.4, U6.12 (PA3)
unnamed: J3.5, U6.10 (PA4)
unnamed: J3.6, U6.9 (PA5)
unnamed: J3.7, U6.8 (PA6)
unnamed: J3.8, U6.7 (PA7)
unnamed: J4.1, U6.27 (PB0)
unnamed: J4.2, U6.28 (PB1)
unnamed: J4.3, U6.29 (PB2)
unnamed: J4.4, U6.30 (PB3)
unnamed: J4.5, U6.31 (PB4)
unnamed: J4.6, U6.32 (PB5)
unnamed: J4.7, U6.33 (PB6)
unnamed: J4.8, U6.34 (PB7)
unnamed: J5.1, U8.20 (P1[0]/TMS/SWDIO)
unnamed: J5.2, U8.21 (P1[1]/TCK/SWDCK)
unnamed: R2.2, U3.6 (IEI)
unnamed: R3.2, U5.18 (CS0), U5.19 (CS1)
unnamed: R5.2, U8.36 (DM/P15[7])
unnamed: R6.2, U8.35 (DP/P15[6])
unnamed: R7.2, U8.90 (P6[1])
unnamed: U8.93 (P15[4]), U10.8 (OUT)
VCC: U3.9 (VCC), U5.24 (VCC), U7.28 (VCC), U9.28 (VCC)

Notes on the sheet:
PSoC Download Connector

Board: 2 copper layers, 47 parts (0 on the bottom side), 115 nets, no tracks yet.
